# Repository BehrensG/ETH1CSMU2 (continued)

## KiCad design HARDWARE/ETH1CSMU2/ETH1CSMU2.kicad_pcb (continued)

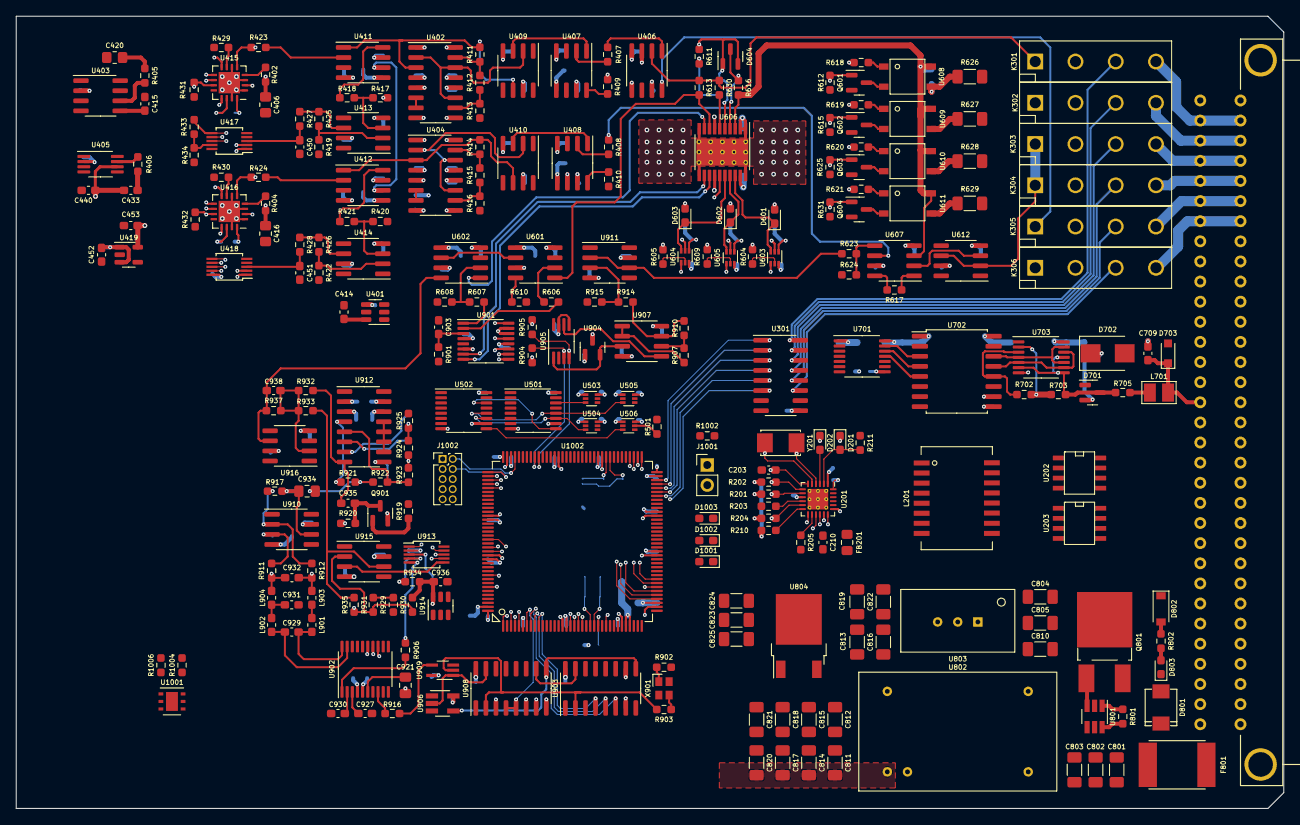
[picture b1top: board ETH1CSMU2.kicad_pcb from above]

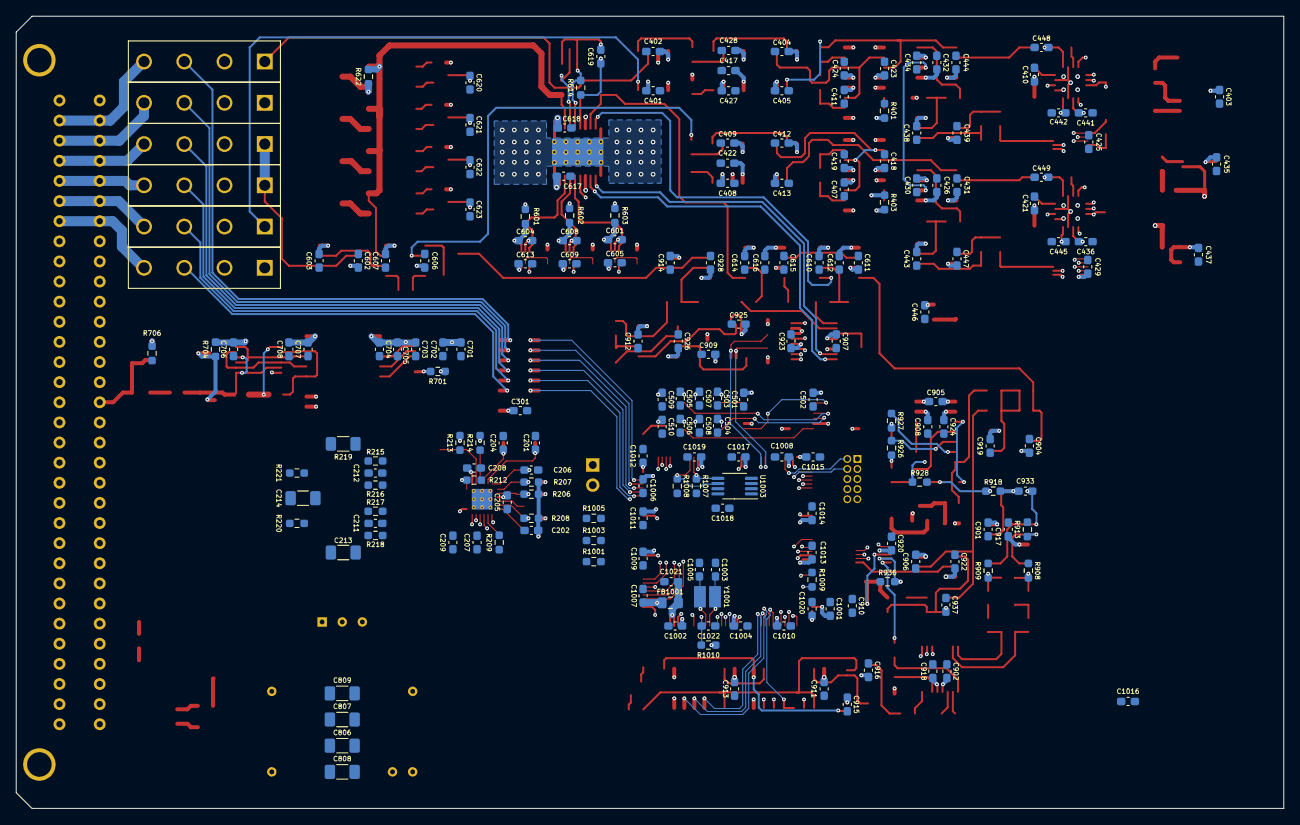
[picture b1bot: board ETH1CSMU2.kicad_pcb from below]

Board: 4 copper layers, 160.0 x 100.0 mm, 446 parts (191 on the bottom side), 310 nets.

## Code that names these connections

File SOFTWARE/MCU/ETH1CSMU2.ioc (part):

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Mcu.Name=STM32F746ZGTx
Mcu.Package=LQFP144
Mcu.UserName=STM32F746ZGTx
PA1.Mode=RMII
PA1.Signal=ETH_REF_CLK
PA11.GPIOParameters=PinState,GPIO_Label
PA11.GPIO_Label=DAC1_nRST
PA11.PinState=GPIO_PIN_SET
PA11.Signal=GPIO_Output
PA12.GPIOParameters=GPIO_Label
PA12.GPIO_Label=DAC1_LDAC
PA12.Signal=GPIO_Output
PA13.Mode=Serial_Wire
PA13.Signal=SYS_JTMS-SWDIO
PA14.Mode=Serial_Wire
PA14.Signal=SYS_JTCK-SWCLK
PA15.GPIOParameters=PinState,GPIO_Label
PA15.GPIO_Label=SPI3_NSS
PA15.PinState=GPIO_PIN_SET
PA15.Signal=GPIO_Output
PA2.Mode=RMII
PA2.Signal=ETH_MDIO
PA4.GPIOParameters=PinState,GPIO_Label
PA4.GPIO_Label=SPI1_NSS
PA4.PinState=GPIO_PIN_SET
PA4.Signal=GPIO_Output
PA5.GPIOParameters=GPIO_Speed
PA5.GPIO_Speed=GPIO_SPEED_FREQ_HIGH
PA5.Mode=Full_Duplex_Master
PA5.Signal=SPI1_SCK
PA6.GPIOParameters=GPIO_Speed
PA6.GPIO_Speed=GPIO_SPEED_FREQ_HIGH
PA6.Mode=Full_Duplex_Master
PA6.Signal=SPI1_MISO
PA7.Mode=RMII
PA7.Signal=ETH_CRS_DV
PA8.Mode=I2C
PA8.Signal=I2C3_SCL
PB10.GPIOParameters=PinState,GPIO_Label
PB10.GPIO_Label=CXN_REL2
PB10.PinState=GPIO_PIN_RESET
PB10.Signal=GPIO_Output
PB11.GPIOParameters=PinState,GPIO_Label
PB11.GPIO_Label=CXN_REL1
PB11.PinState=GPIO_PIN_RESET
PB11.Signal=GPIO_Output
PB12.GPIOParameters=PinState,GPIO_Label
PB12.GPIO_Label=SPI2_NSS
PB12.PinState=GPIO_PIN_SET
PB12.Signal=GPIO_Output
PB13.Mode=Full_Duplex_Master
PB13.Signal=SPI2_SCK
PB14.Mode=Full_Duplex_Master
PB14.Signal=SPI2_MISO
PB15.Mode=Full_Duplex_Master
PB15.Signal=SPI2_MOSI
PB2.GPIOParameters=PinState,GPIO_Label
PB2.GPIO_Label=LED_BLUE
PB2.PinState=GPIO_PIN_SET
PB2.Signal=GPIO_Output
PB5.GPIOParameters=GPIO_Speed
PB5.GPIO_Speed=GPIO_SPEED_FREQ_HIGH
PB5.Mode=Full_Duplex_Master
PB5.Signal=SPI1_MOSI
PC1.Mode=RMII
PC1.Signal=ETH_MDC
PC10.GPIOParameters=GPIO_Speed,GPIO_PuPd
PC10.GPIO_PuPd=GPIO_PULLUP
PC10.GPIO_Speed=GPIO_SPEED_FREQ_HIGH
PC10.Mode=Full_Duplex_Master
PC10.Signal=SPI3_SCK
PC11.GPIOParameters=GPIO_Speed
PC11.GPIO_Speed=GPIO_SPEED_FREQ_HIGH
PC11.Mode=Full_Duplex_Master
PC11.Signal=SPI3_MISO
PC12.GPIOParameters=GPIO_Speed
PC12.GPIO_Speed=GPIO_SPEED_FREQ_HIGH
PC12.Mode=Full_Duplex_Master
PC12.Signal=SPI3_MOSI
PC13.GPIOParameters=PinState,GPIO_Label
PC13.GPIO_Label=FGEN_nDIV10
PC13.PinState=GPIO_PIN_SET
PC13.Signal=GPIO_Output
PC14/OSC32_IN.GPIOParameters=PinState,GPIO_Label
PC14/OSC32_IN.GPIO_Label=FGEN_DIV8
PC14/OSC32_IN.PinState=GPIO_PIN_SET
PC14/OSC32_IN.Signal=GPIO_Output
PC15/OSC32_OUT.GPIOParameters=PinState,GPIO_Label
PC15/OSC32_OUT.GPIO_Label=FGEN_DIV4
PC15/OSC32_OUT.PinState=GPIO_PIN_SET
PC15/OSC32_OUT.Signal=GPIO_Output
PC4.Mode=RMII
PC4.Signal=ETH_RXD0
PC5.Mode=RMII
PC5.Signal=ETH_RXD1
PC9.Mode=I2C
PC9.Signal=I2C3_SDA
PD0.GPIOParameters=GPIO_Label
PD0.GPIO_Label=ADC1_RVS1
PD0.Signal=GPIO_Input
PD1.GPIOParameters=GPIO_Label
PD1.GPIO_Label=ADC1_RVS2
PD1.Signal=GPIO_Input
PD10.GPIOParameters=GPIO_Label
PD10.GPIO_Label=MCU_nISNK
PD10.Signal=GPXTI10
PD11.GPIOParameters=GPIO_Label
PD11.GPIO_Label=MCU_nISRC
PD11.Signal=GPXTI11
PD12.Mode=I2C
PD12.Signal=I2C4_SCL
PD13.Mode=I2C
PD13.Signal=I2C4_SDA
PD14.GPIOParameters=GPIO_Label
PD14.GPIO_Label=SR_OUT
PD14.Signal=GPIO_Input
PD15.GPIOParameters=GPIO_Label
PD15.GPIO_Label=SR_LAT
PD15.Signal=GPIO_Output
PD9.GPIOParameters=GPIO_Label
PD9.GPIO_Label=MCU_nTDS
PD9.Signal=GPXTI9
PE10.GPIOParameters=GPIO_Label
PE10.GPIO_Label=MCU_DEFAULT
PE10.Signal=GPIO_Input
PE12.GPIOParameters=GPIO_Label
PE12.GPIO_Label=CXN_REL6
PE12.Signal=GPIO_Output
PE13.GPIOParameters=GPIO_Label
PE13.GPIO_Label=CXN_REL5
PE13.Signal=GPIO_Output
PE14.GPIOParameters=GPIO_Label
PE14.GPIO_Label=CXN_REL4
PE14.Signal=GPIO_Output
PE15.GPIOParameters=GPIO_Label
PE15.GPIO_Label=CXN_REL3
PE15.Signal=GPIO_Output
PE2.Mode=RX_Only_Simplex_Unidirect_Master
PE2.Signal=SPI4_SCK
PE4.GPIOParameters=PinState,GPIO_Label
PE4.GPIO_Label=SPI4_NSS
PE4.PinState=GPIO_PIN_RESET
PE4.Signal=GPIO_Output
PE5.Mode=RX_Only_Simplex_Unidirect_Master
PE5.Signal=SPI4_MISO
PE7.GPIOParameters=GPIO_Label
PE7.GPIO_Label=TRIG_IN
PE7.Signal=GPXTI7
PE8.GPIOParameters=GPIO_Label
PE8.GPIO_Label=TRIG_OUT
PE8.Signal=GPIO_Output
PE9.GPIOParameters=GPIO_Label
PE9.GPIO_Label=TRIG_EN
PE9.Signal=GPIO_Output
PF0.GPIOParameters=PinState,GPIO_Label
PF0.GPIO_Label=FGEN_DIV2
PF0.PinState=GPIO_PIN_SET
PF0.Signal=GPIO_Output
PF11.GPIOParameters=PinState,GPIO_Label
PF11.GPIO_Label=LED_RED
PF11.PinState=GPIO_PIN_SET
PF11.Signal=GPIO_Output
PF12.GPIOParameters=PinState,GPIO_Label
PF12.GPIO_Label=LED_GREEN
PF12.PinState=GPIO_PIN_SET
PF12.Signal=GPIO_Output
PF6.GPIOParameters=GPIO_Speed,PinState,GPIO_Label
PF6.GPIO_Label=SPI5_NSS
PF6.GPIO_Speed=GPIO_SPEED_FREQ_HIGH
PF6.PinState=GPIO_PIN_SET
PF6.Signal=GPIO_Output
PF7.Mode=Full_Duplex_Master
PF7.Signal=SPI5_SCK
PF8.Mode=Full_Duplex_Master
PF8.Signal=SPI5_MISO
PF9.Mode=Full_Duplex_Master
PF9.Signal=SPI5_MOSI
PG11.Mode=RMII
PG11.Signal=ETH_TX_EN
PG12.GPIOParameters=GPIO_Speed,PinState,GPIO_Label
PG12.GPIO_Label=DAC2_nLDAC
PG12.GPIO_Speed=GPIO_SPEED_FREQ_HIGH
PG12.PinState=GPIO_PIN_SET
PG12.Signal=GPIO_Output
PG13.Mode=RMII
PG13.Signal=ETH_TXD0
PG14.Mode=RMII
PG14.Signal=ETH_TXD1
PG2.GPIOParameters=GPIO_Label
PG2.GPIO_Label=SR_CLK
PG2.Signal=GPIO_Output
PG3.GPIOParameters=GPIO_Label
PG3.GPIO_Label=SR_DAT
PG3.Signal=GPIO_Output
PG4.GPIOParameters=PinState,GPIO_Label
PG4.GPIO_Label=EEPROM_WP
PG4.PinState=GPIO_PIN_SET
PG4.Signal=GPIO_Output
PG5.GPIOParameters=GPIO_Label
PG5.GPIO_Label=MCU_CURR_SENS_1kR
PG5.Signal=GPIO_Output
PG6.GPIOParameters=PinState,GPIO_Label
PG6.GPIO_Label=MCU_CURR_SENS_100R
PG6.PinState=GPIO_PIN_RESET
PG6.Signal=GPIO_Output
PG7.GPIOParameters=PinState,GPIO_Label
PG7.GPIO_Label=MCU_CURR_SENS_10R
PG7.PinState=GPIO_PIN_RESET
PG7.Signal=GPIO_Output
PG8.GPIOParameters=PinState,GPIO_Label
PG8.GPIO_Label=MCU_CURR_SENS_1R
PG8.PinState=GPIO_PIN_SET
PG8.Signal=GPIO_Output
RCC.HSE_VALUE=8000000
RCC.SYSCLKFreq_VALUE=216000000
RCC.SYSCLKSource=RCC_SYSCLKSOURCE_PLLCLK
board=custom

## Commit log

2022-08-07 Hardware design
2022-08-09 Hardware design.
2022-08-10 Schematic
2022-08-11 Hardware and software development
2022-08-11 CRC check
2022-08-14 PCB layout
2022-08-15 Changes in schematic.
2022-08-26 Bug fixes.
2022-08-26 Schematic modification and GPIO setup.
2022-08-29 Added two 10uF capacitors in Frontend page.
2023-01-22 Software development
2023-01-27 Software development. Ethernet works.
2023-03-04 Converter HW to KiCAD 7.0. Fixed 3D model paths.
2023-03-26 Software development and hardware changes.
2023-03-27 Software development, added comments to schematic.
2023-04-01 Software development and hardware changes. FGEN code works.
2023-04-02 Development
2023-04-18 AD7980 test works.
2023-04-19 Software development.
2023-05-07 ThreadX software development.
2023-05-10 ThreadX TCP server works.
2023-05-11 Imported code from _FreeRTOS
2023-05-12 Development of FreeRTOS code
2023-05-16 Software developement
2023-05-17 Sofware development
2023-05-19 Calibration software development. Problems with positive voltage. Need to add gain calibration.
2023-05-20 DC calibration works. AC signal function works.
2023-07-10 Software
2023-07-12 Hardware fix. Created README file
2023-07-12 Added README and images
